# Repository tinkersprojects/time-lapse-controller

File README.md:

# programable Time Lapse Controller
[https://tinkersprojects.com/](https://tinkersprojects.com/)

This is a programable time lapse for a Go-Pro where tiles on the track deterands how it moves. The system can move in backward/forwards, rotate the camera and soon tilt the camera (when i get more time). It uses Lego train track as the track to guide it along and place programing tiles. The tiles are different colors which get a colour sensor reads and changes moving mode.

Currently there are 4 colours with 4 different modes. Green (also starting mode) is full travel speed with no other movements. Blue is start rotation of camera. Yellow is half the speed. Red is stop. More colours will be added soon.
The wheels are held in place with 2 x 20mmxM3 screws and driven by a 28byj-48 stepper motor. The system can be run from a 9V battery but cannot last long with out being replaced.

The PCB can be purchased from https://tinkersprojects.com/product/time-lapse-controller/

## Keep up to date
New Parts will be added, Keep up to date by following:
- Project page -> http://tinkersprojects.com/project/programable-time-lapse/
- This Thing -> https://www.thingiverse.com/thing:2825424
- my Profile -> https://www.thingiverse.com/haybailes/about

## See Other Projects
Have a look at this and other projects that I have done: http://tinkersprojects.com/

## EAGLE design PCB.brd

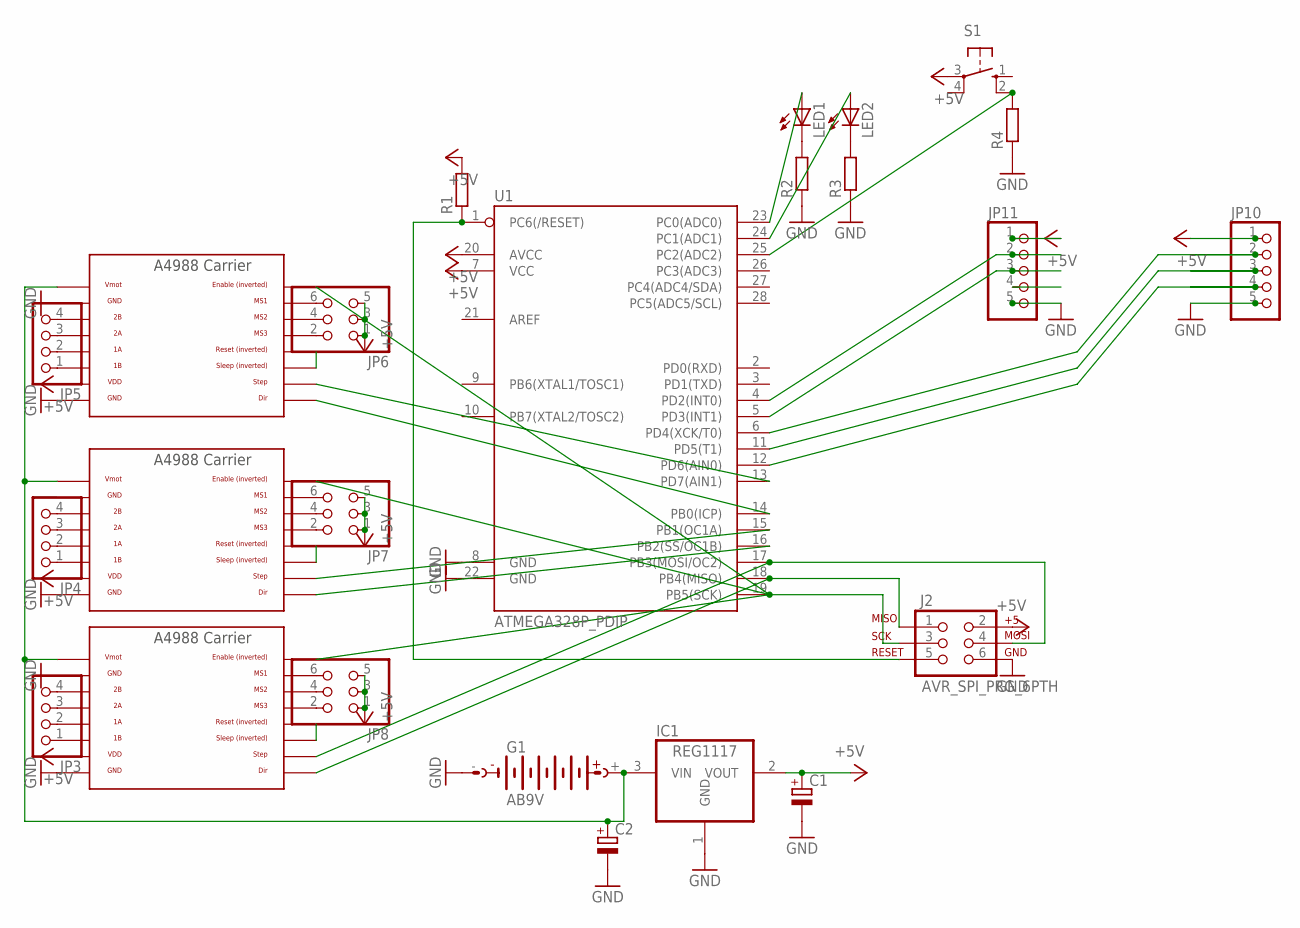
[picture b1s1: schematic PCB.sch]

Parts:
C1, C2: CPOL-EUE3.5-8; E3,5-8
G1: AB9V
IC1: REG1117; SOT223
J2: AVR_SPI_PRG_6PTH; 2X3
JP3, JP4, JP5: PINHD-1X4; 1X04
JP6, JP7, JP8: PINHD-2X3; 2X03
JP10, JP11: PINHD-1X5; 1X05
LED1, LED2: LED5MM
R1, R2, R3, R4: R-EU_0207/10; 0207/10
S1: 10-XX; B3F-10XX
U1: ATMEGA328P_PDIP; DIL28-3
U$1, U$2, U$4: A4988BREAKOUT

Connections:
+5V: C1.+, IC1.2 (VOUT), J2.2, JP6.1, JP6.3, JP6.5, JP7.1, JP7.3, JP7.5, JP8.1, JP8.3, JP8.5, JP10.1, JP11.1, R1.2, S1.3, U1.7 (VCC), U1.20 (AVCC), U$1.VDD, U$2.VDD, U$4.VDD
GND: C1.-, C2.-, G1.-, IC1.1 (GND), J2.6, JP10.5, JP11.5, R2.1, R3.1, R4.1, U1.8 (GND), U1.22 (GND), U$1.GND, U$1.GND@0 (GND), U$2.GND, U$2.GND@0 (GND), U$4.GND, U$4.GND@0 (GND)
unnamed: U$1.RST, U$1.SLP (SLEEP)
unnamed: U$2.RST, U$2.SLP (SLEEP)
unnamed: C2.+, G1.+, IC1.3 (VIN), U$1.VMOT, U$2.VMOT, U$4.VMOT
unnamed: J2.1, U1.18 (PB4(MISO)), U$2.DIR
unnamed: J2.3, U1.19 (PB5(SCK)), U$1.EN, U$2.EN, U$4.EN
unnamed: J2.4, U1.17 (PB3(MOSI/OC2)), U$2.STEP
unnamed: J2.5, R1.1, U1.1 (PC6(/RESET))
unnamed: JP3.1, U$2.1B
unnamed: JP3.2, U$2.1A
unnamed: JP3.3, U$2.2A
unnamed: JP3.4, U$2.2B
unnamed: JP4.1, U$1.1B
unnamed: JP4.2, U$1.1A
unnamed: JP4.3, U$1.2A
unnamed: JP4.4, U$1.2B
unnamed: JP5.1, U$4.1B
unnamed: JP5.2, U$4.1A
unnamed: JP5.3, U$4.2A
unnamed: JP5.4, U$4.2B
unnamed: JP6.2, U$4.MS3
unnamed: JP6.4, U$4.MS2
unnamed: JP6.6, U$4.MS1
unnamed: JP7.2, U$1.MS3
unnamed: JP7.4, U$1.MS2
unnamed: JP7.6, U$1.MS1
unnamed: JP8.2, U$2.MS3
unnamed: JP8.4, U$2.MS2
unnamed: JP8.6, U$2.MS1
unnamed: JP11.2, U1.4 (PD2(INT0))
unnamed: JP11.3, U1.5 (PD3(INT1))
unnamed: JP10.2, U1.6 (PD4(XCK/T0))
unnamed: JP10.3, U1.11 (PD5(T1))
unnamed: JP10.4, U1.12 (PD6(AIN0))
unnamed: U1.13 (PD7(AIN1)), U$4.STEP
unnamed: U1.14 (PB0(ICP)), U$4.DIR
unnamed: U$4.RST, U$4.SLP (SLEEP)
unnamed: U1.15 (PB1(OC1A)), U$1.STEP
unnamed: U1.16 (PB2(SS/OC1B)), U$1.DIR
unnamed: LED1.A, U1.23 (PC0(ADC0))
unnamed: LED2.A, U1.24 (PC1(ADC1))
unnamed: LED1.K (C), R2.2
unnamed: LED2.K (C), R3.2
unnamed: R4.2, S1.2 (S1), U1.25 (PC2(ADC2))

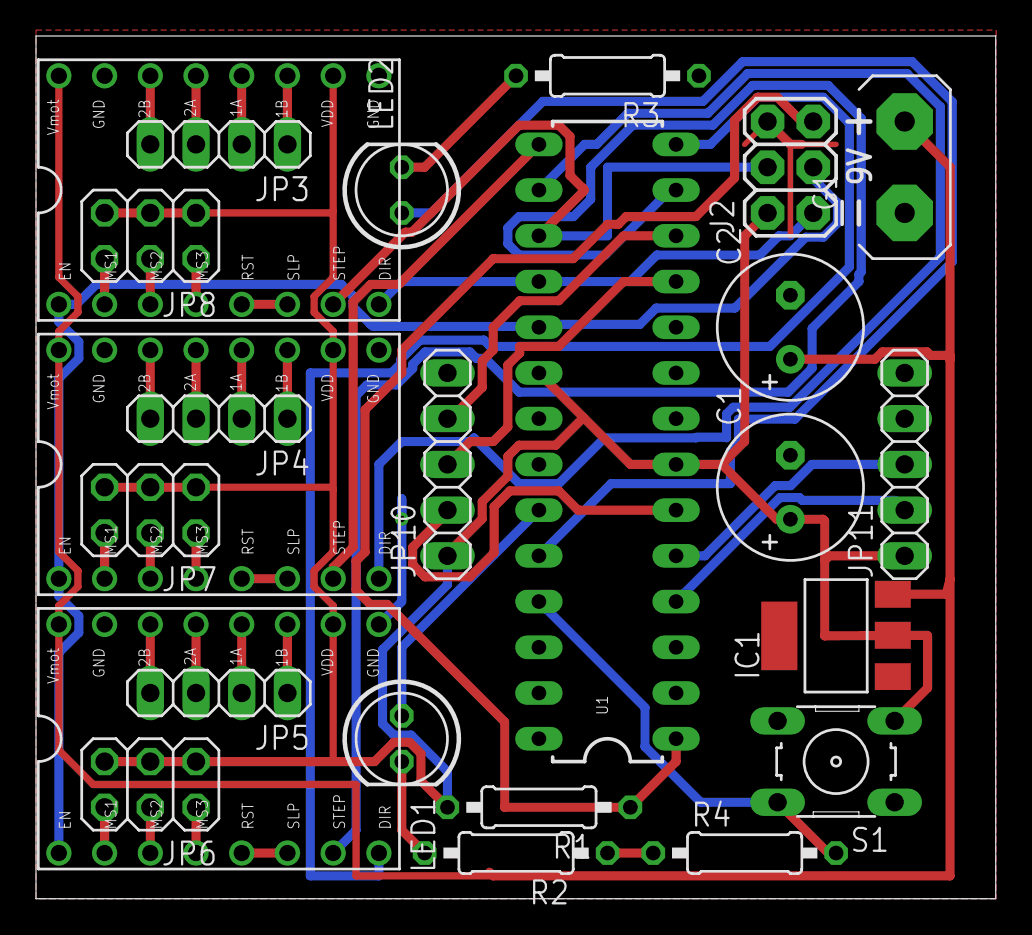
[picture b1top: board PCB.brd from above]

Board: 2 copper layers, 53.3 x 47.9 mm, 24 parts (0 on the bottom side), 45 nets.

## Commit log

2018-04-12 Add files via upload
    files upload
2018-04-12 Add files via upload
    Arduino files upload

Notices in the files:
parts and their libraries:
SparkFun-Connectors: Licensing: Creative Commons ShareAlike 4.0 International - https://creativecommons.org/licenses/by-sa/4.0
